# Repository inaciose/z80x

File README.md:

# z80x
SBCs &amp; MBCs and other Z80 explorations    

# Z80_SBC1
3.6864Mz, 16KB ROM, 32K RAM and serial MC68B50 (0x80) 57600bps (115200 c/ o dobro do relógio)  

ROM 9B000000.BIN with (RC2014 versions):  
- SCM-Small Computer Monitor  
- MS-BASIC  

# Z80_SBC2
3.6864Mz, 16KB (0KB paged) ROM, 48KB (64KB paged) RAM and serial MC68B50 (0x80) 57600bps  
Pageable ROM/RAML16K (0x38 toggle page, 0x30 reset page)  

Same ROM as Z80_SBC1 (or the one with CP/M 2.2 bootloader ?)

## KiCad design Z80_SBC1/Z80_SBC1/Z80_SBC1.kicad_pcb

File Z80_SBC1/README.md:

# Z80_SBC1

3.6864Mz, 16KB ROM, 32K RAM and serial MC68B50 (0x80) 57600bps 8N1 (115200 c/ o dobro do relógio)  

ROM 9B000000.BIN with (RC2014 versions):  
- 0000-1FFF: SCM-Small Computer Monitor  
- 2000-3FFF: MS-BASIC  

Press reset after power on (the reset circuit must be revised)

Help (commands): help  
MS-BASIC: G 2000  
Exit MS-BASIC: monitor  

# Equations  
MEMRD = MREQ_ + RD_  
MEMWR = MREQ_ + WR_  

ROM_CE = A14 + A15  
ROM_OE = MEMRD  

RAM_CE = not(A15)  
RAM_OE = MEMRD  
RAM_WE = MEMWR  

ACIA = A7 x not(A6) (10XX XXXX, 0x80 com replicas, RC2014 MC68B50 serial module)  

# Notes
Based on Searle Grants Minimal Z80 with 8KB ROM, 32K RAM and serial MC68B50.  
http://searle.x10host.com/z80/SimpleZ80_32K.html

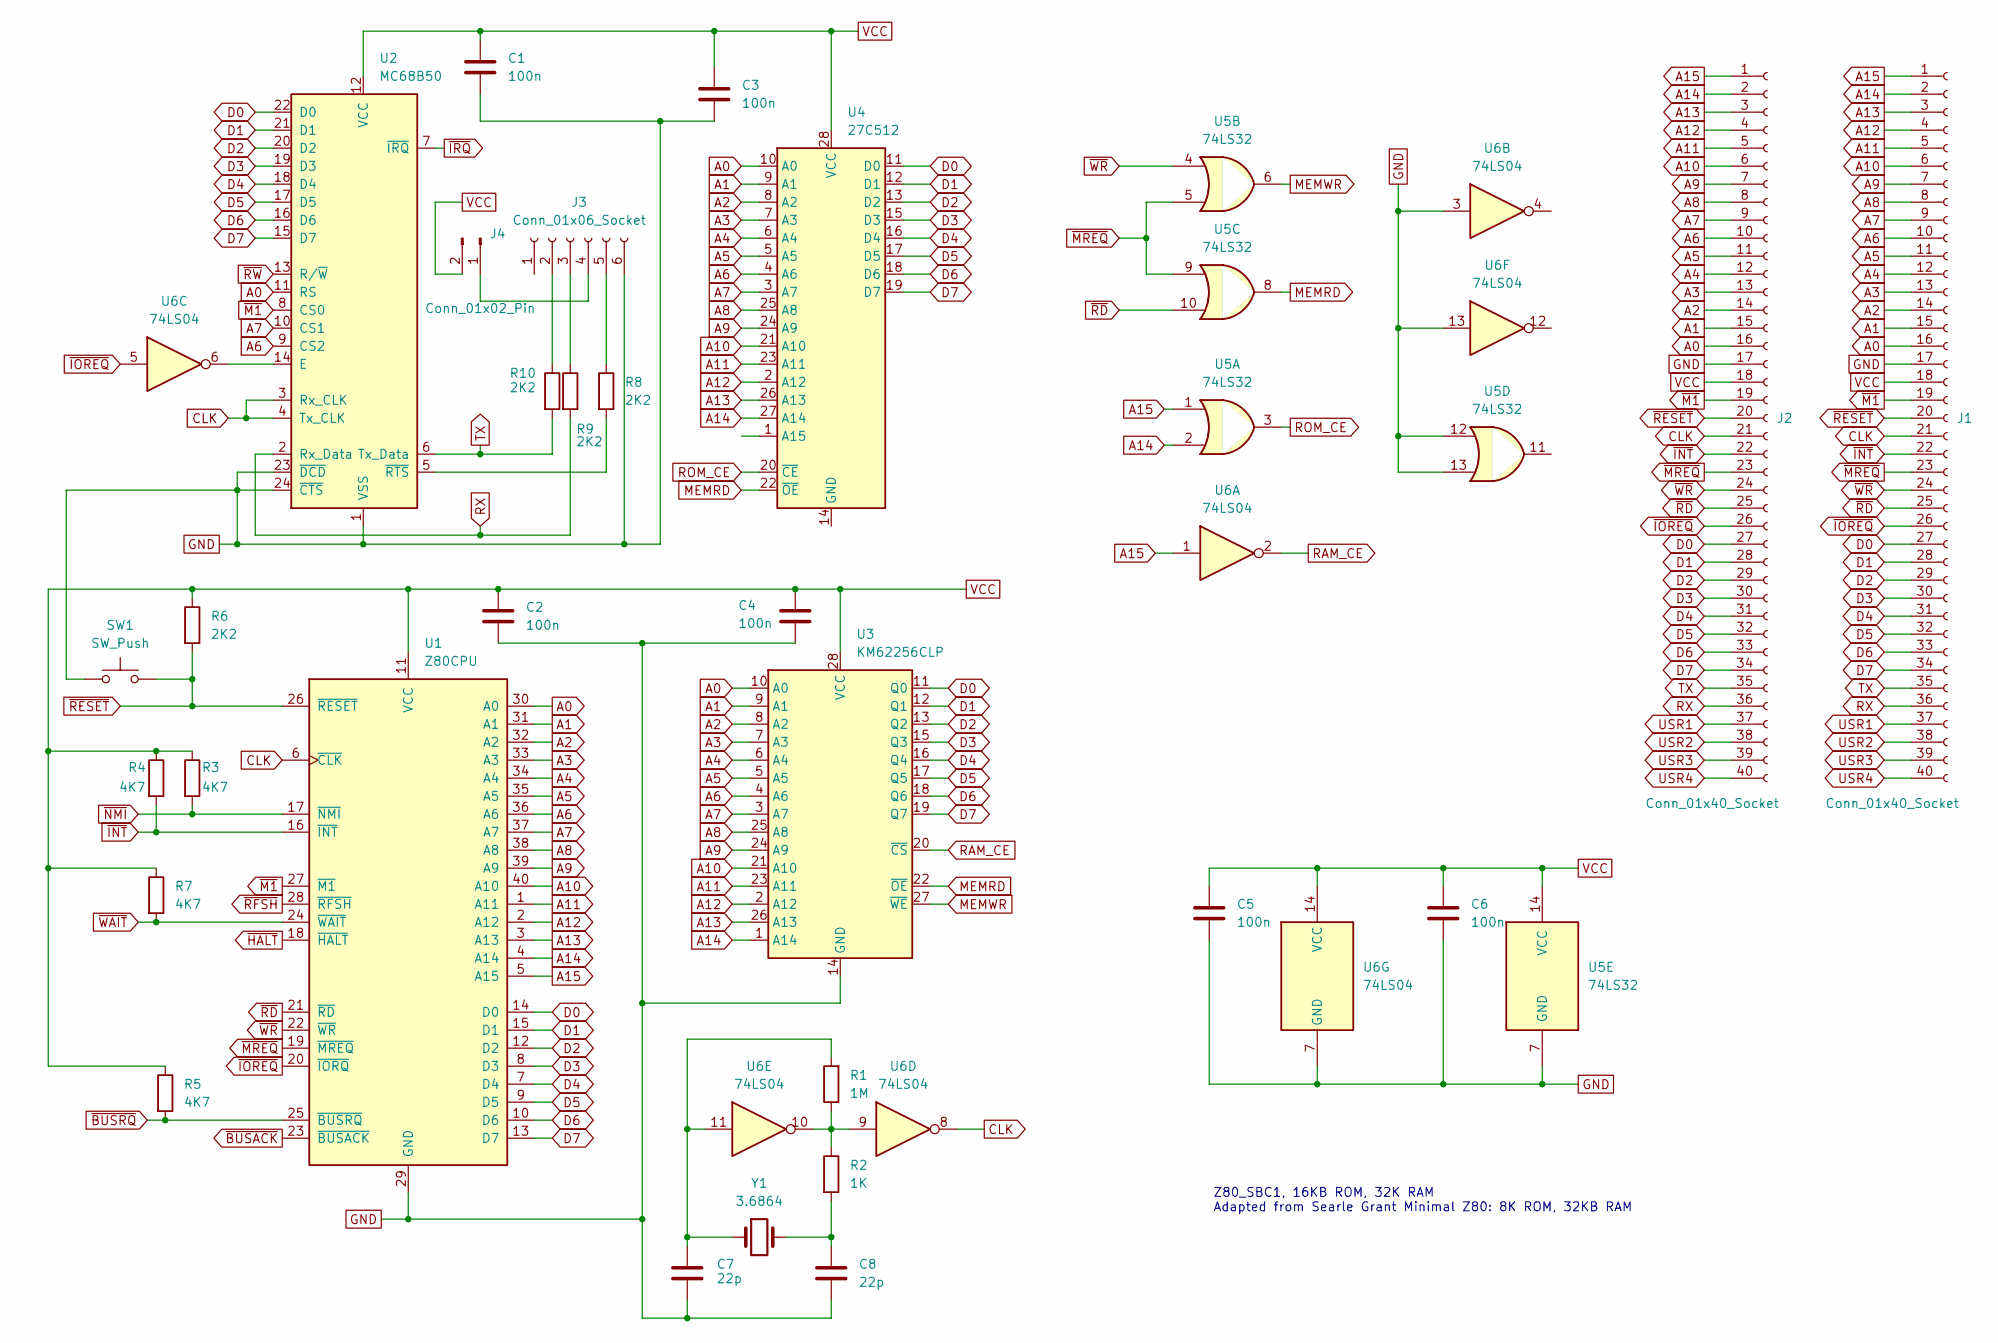
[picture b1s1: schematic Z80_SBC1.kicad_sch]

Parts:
C1, C2, C3, C4, C5, C6: 100n; C_Disc_D5.1mm_W3.2mm_P5.00mm
C7, C8: 22p; C_Disc_D3.0mm_W2.0mm_P2.50mm
J1: Conn_01x40_Socket; PinHeader_1x40_P2.54mm_Horizontal
J2: Conn_01x40_Socket; PinHeader_1x40_P2.54mm_Vertical
J3: Conn_01x06_Socket; PinHeader_1x06_P2.54mm_Horizontal
J4: Conn_01x02_Pin; PinHeader_1x02_P2.54mm_Vertical
R1: 1M; R_Axial_DIN0207_L6.3mm_D2.5mm_P7.62mm_Horizontal
R2: 1K; R_Axial_DIN0207_L6.3mm_D2.5mm_P7.62mm_Horizontal
R3, R4, R5, R7: 4K7; R_Axial_DIN0207_L6.3mm_D2.5mm_P7.62mm_Horizontal
R6, R8, R9, R10: 2K2; R_Axial_DIN0207_L6.3mm_D2.5mm_P7.62mm_Horizontal
SW1: SW_Push; SW_Tactile_Straight_KSA0Axx1LFTR
U1: Z80CPU; DIP-40_W15.24mm_Socket_LongPads
U2: MC68B50; DIP-24_W15.24mm
U3: KM62256CLP; DIP-28_W15.24mm
U4: 27C512; DIP-28_W15.24mm
U5: 74LS32; DIP-14_W7.62mm_LongPads
U6: 74LS04; DIP-14_W7.62mm_LongPads
Y1: 3.6864; Crystal_HC18-U_Vertical

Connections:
A0: J1.16, J2.16, U1.30 (A0), U2.11 (RS), U3.10 (A0), U4.10 (A0)
A1: J1.15, J2.15, U1.31 (A1), U3.9 (A1), U4.9 (A1)
A2: J1.14, J2.14, U1.32 (A2), U3.8 (A2), U4.8 (A2)
A3: J1.13, J2.13, U1.33 (A3), U3.7 (A3), U4.7 (A3)
A4: J1.12, J2.12, U1.34 (A4), U3.6 (A4), U4.6 (A4)
A5: J1.11, J2.11, U1.35 (A5), U3.5 (A5), U4.5 (A5)
A6: J1.10, J2.10, U1.36 (A6), U2.9 (CS2), U3.4 (A6), U4.4 (A6)
A7: J1.9, J2.9, U1.37 (A7), U2.10 (CS1), U3.3 (A7), U4.3 (A7)
A8: J1.8, J2.8, U1.38 (A8), U3.25 (A8), U4.25 (A8)
A9: J1.7, J2.7, U1.39 (A9), U3.24 (A9), U4.24 (A9)
A10: J1.6, J2.6, U1.40 (A10), U3.21 (A10), U4.21 (A10)
A11: J1.5, J2.5, U1.1 (A11), U3.23 (A11), U4.23 (A11)
A12: J1.4, J2.4, U1.2 (A12), U3.2 (A12), U4.2 (A12)
A13: J1.3, J2.3, U1.3 (A13), U3.26 (A13), U4.26 (A13)
A14: J1.2, J2.2, U1.4 (A14), U3.1 (A14), U4.27 (A14), U5.2
A15: J1.1, J2.1, U1.5 (A15), U5.1, U6.1
CLK: J1.21, J2.21, U1.6 (~CLK), U2.3 (Rx_CLK), U2.4 (Tx_CLK), U6.8
D0: J1.27, J2.27, U1.14 (D0), U2.22 (D0), U3.11 (Q0), U4.11 (D0)
D1: J1.28, J2.28, U1.15 (D1), U2.21 (D1), U3.12 (Q1), U4.12 (D1)
D2: J1.29, J2.29, U1.12 (D2), U2.20 (D2), U3.13 (Q2), U4.13 (D2)
D3: J1.30, J2.30, U1.8 (D3), U2.19 (D3), U3.15 (Q3), U4.15 (D3)
D4: J1.31, J2.31, U1.7 (D4), U2.18 (D4), U3.16 (Q4), U4.16 (D4)
D5: J1.32, J2.32, U1.9 (D5), U2.17 (D5), U3.17 (Q5), U4.17 (D5)
D6: J1.33, J2.33, U1.10 (D6), U2.16 (D6), U3.18 (Q6), U4.18 (D6)
D7: J1.34, J2.34, U1.13 (D7), U2.15 (D7), U3.19 (Q7), U4.19 (D7)
GND: C1.2, C2.2, C3.2, C4.2, C5.2, C6.2, C7.2, C8.2, J1.17, J2.17, J3.6, SW1.1, U1.29 (GND), U2.1 (VSS), U2.23 (~DCD), U2.24 (~CTS), U3.14 (GND), U5.7 (GND), U5.12, U5.13, U6.3, U6.7 (GND), U6.13
MEMRD: U3.22 (~OE), U4.22 (~OE), U5.8
MEMWR: U3.27 (~WE), U5.6
unnamed: C7.1, R1.2, U6.11, Y1.1
unnamed: C8.1, R2.2, Y1.2
unnamed: J3.2, R10.1
unnamed: J3.3, R9.1
unnamed: J3.4, J4.1
unnamed: J3.5, R8.1
unnamed: R1.1, R2.1, U6.9, U6.10
unnamed: U2.14 (E), U6.6
unnamed: R8.2, U2.5 (~RTS)
RAM_CE: U3.20 (~CS), U6.2
ROM_CE: U4.20 (~CE), U5.3
RX: J1.36, J2.36, R9.2, U2.2 (Rx_Data)
TX: J1.35, J2.35, R10.2, U2.6 (Tx_Data)
USR1: J1.37, J2.37
USR2: J1.38, J2.38
USR3: J1.39, J2.39
USR4: J1.40, J2.40
VCC: C1.1, C2.1, C3.1, C4.1, C5.1, C6.1, J1.18, J2.18, J4.2, R3.1, R4.1, R5.1, R6.1, R7.1, U1.11 (VCC), U2.12 (VCC), U3.28 (VCC), U4.28 (VCC), U5.14 (VCC), U6.14 (VCC)
~BUSACK: U1.23 (~BUSACK)
~BUSRQ: R5.2, U1.25 (~BUSRQ)
~HALT: U1.18 (~HALT)
~INT: J1.22, J2.22, R4.2, U1.16 (~INT)
~IOREQ: J1.26, J2.26, U1.20 (~IORQ), U6.5
~IRQ: U2.7 (~IRQ)
~M1: J1.19, J2.19, U1.27 (~M1), U2.8 (CS0)
~MREQ: J1.23, J2.23, U1.19 (~MREQ), U5.5, U5.9
~NMI: R3.2, U1.17 (~NMI)
~RD: J1.25, J2.25, U1.21 (~RD), U5.10
~RESET: J1.20, J2.20, R6.2, SW1.2, U1.26 (~RESET)
~RFSH: U1.28 (~RFSH)
~RW: U2.13 (R/~W)
~WAIT: R7.2, U1.24 (~WAIT)
~WR: J1.24, J2.24, U1.22 (~WR), U5.4

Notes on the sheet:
Z80_SBC1, 16KB ROM, 32K RAM Adapted from Searle Grant Minimal Z80: 8K ROM, 32KB RAM

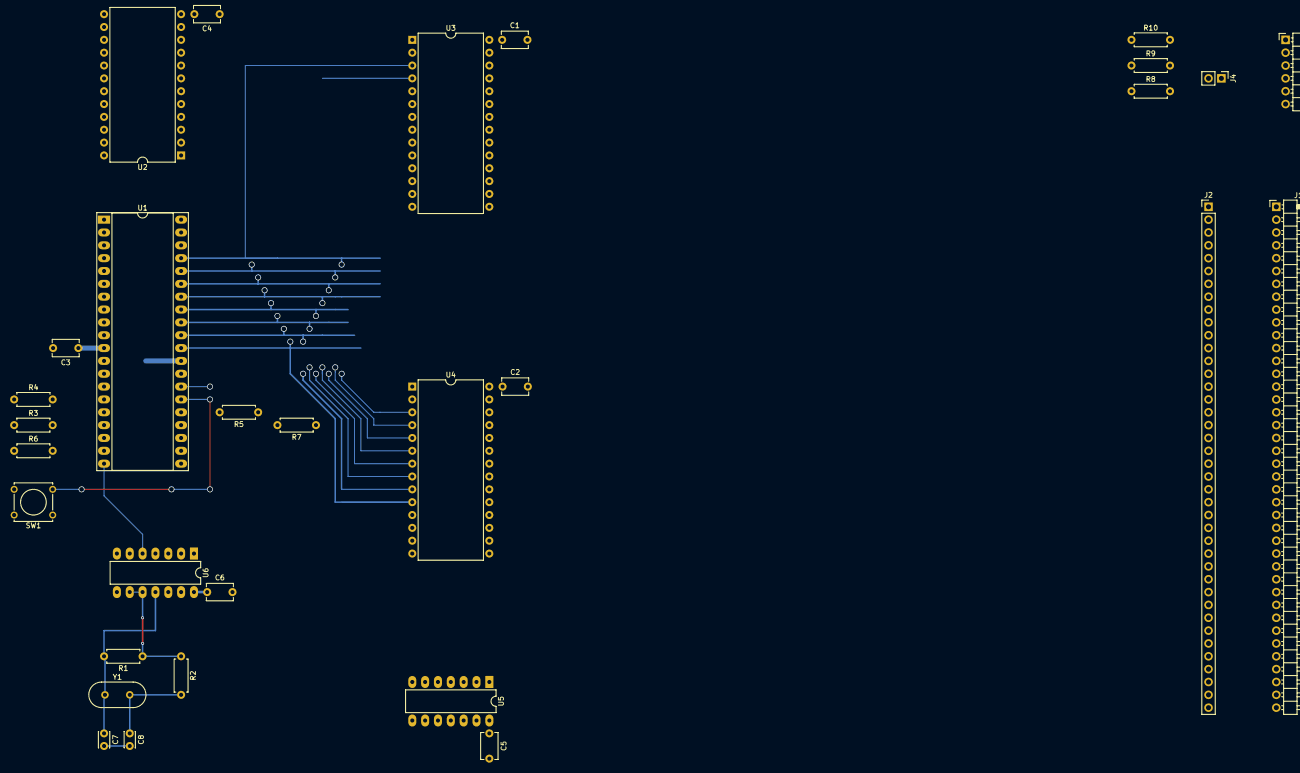
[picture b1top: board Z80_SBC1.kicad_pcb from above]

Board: 2 copper layers, 30 parts (0 on the bottom side), 56 nets.

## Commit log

2025-09-13 first upload
2025-09-13 breadboard img rename and move
2025-09-14 rom2ram and readme
2025-09-14 readme update
